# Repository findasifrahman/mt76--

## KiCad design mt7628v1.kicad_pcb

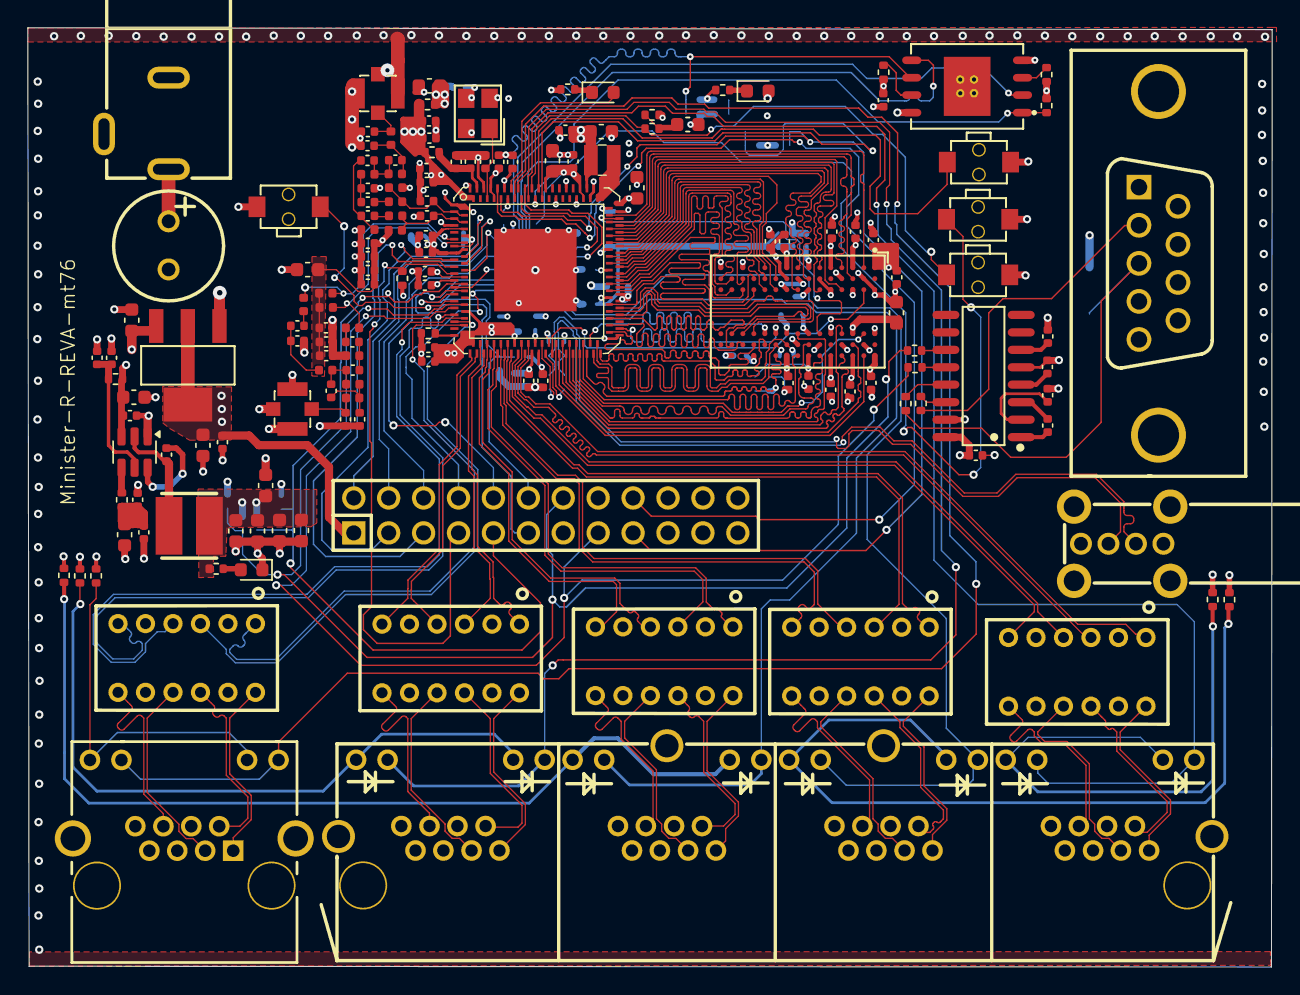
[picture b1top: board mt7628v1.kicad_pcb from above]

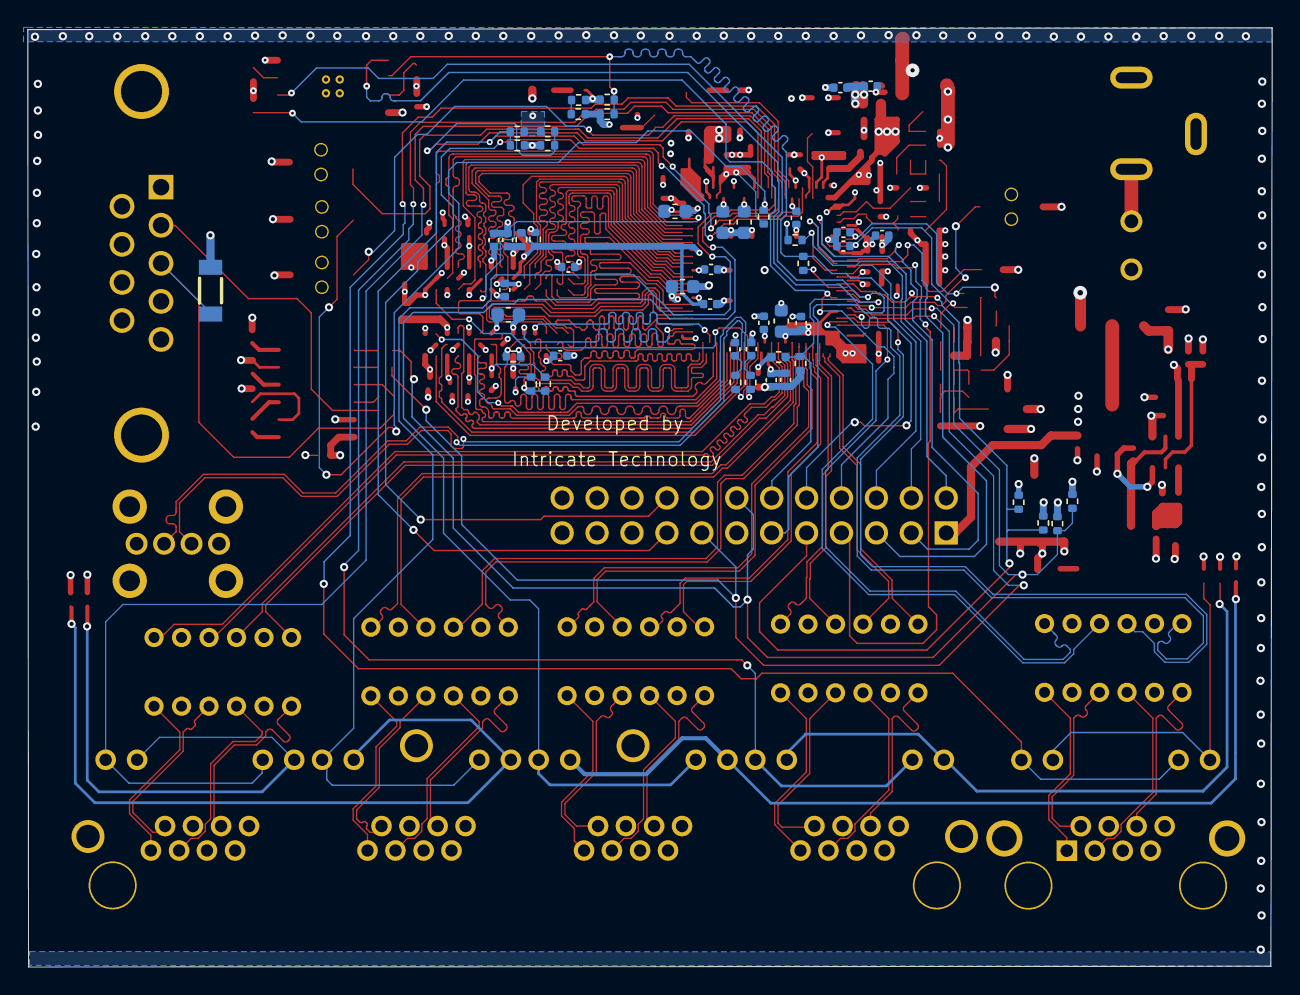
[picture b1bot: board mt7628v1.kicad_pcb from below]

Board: 4 copper layers, 90.5 x 68.3 mm, 201 parts (50 on the bottom side), 176 nets.

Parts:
C1, C2, C4, C5, C6, C7, C14, C15, C16, C18, C21, C25, C26, C29, C34, C35, C36, C37, C38, C39, C40, C70, C71, C76, C85, C95, C96, C97, C98, C99: 100nf/16v; C_0402_1005Metric
C3, C19, C20, C22, C32, C33, C77: 4.7uf/6.3v; C_0603_1608Metric
C8, C10, C11, C17, C30, C43, C45, C47, C48, C51, C61, C66, C81, C82: 1uf/6.3v; C_0402_1005Metric
C9, C27: 2.2uF/6.3V; C_0603_1608Metric
C12, C13: 1.5nf/50V; C_0402_1005Metric
C23, C24: 5pf/50v NC; C_0402_1005Metric
C28, C41, C75: 10uf/6.3v; C_0603_1608Metric
C31: 2.2uf/6.3v; C_0603_1608Metric
C42, C52, C59, C100, C101: 10pf/50v; C_0402_1005Metric
C44, C46, C50, C60, C64, C65, C67, C69, C83: 100pf/50v; C_0402_1005Metric
C49: 10uf/6.3v NC; C_0603_1608Metric
C53, C62, C102, C103: 1.2pf/50v; C_0402_1005Metric
C54, C56, C79, C80: 2pf/50v; C_0402_1005Metric
C55, C104: 9pf/50v; C_0402_1005Metric
C57, C58, C105, C106: 1.8Pf/50v; C_0402_1005Metric
C63: 1.3pf/50v; C_0402_1005Metric
C72, C73: 15pf/50v; C_0402_1005Metric
C74, C89, C90, C91, C92, C93: 22uf/25v; C_0603_1608Metric
C78: 470uf/25v; CAP-TH_BD8.0-P3.50-D0.6-FD
C84: 10uf/25v; C_0603_1608Metric
C86, C87, C94: NC; C_0402_1005Metric
C88: 1uf/25v; C_0402_1005Metric
D1, D2: LED0; LED_0603_1608Metric
D3: LED; D_0603_1608Metric
D4: ZMM5V1; LL-34_L3.5-W1.5-RD
J1: Barrel_Jack_Switch; DC-IN-TH_DC-005C-20A
J2: DE9_Pins; HDR-TH_HL-DP9HB180F
J3: Conn_01x24_MountingPin; HDR-TH_24P-P2.54-V-M-R2-C12-S2.54
J4: RJ45_LED_Shielded_x2; RJ45-TH_DS1128-09-S8B8X
L1: 2.2 uH/VLS252012ET-2R2M; IND-SMD_L2.5-W2.0_VLS2520X
L2, L3, L10, L12: 10nh; L_0402_1005Metric
L4, L9, L15, L16: 2.7nh; L_0402_1005Metric
L5, L7, L8, L13, L14, L18: 2nh; L_0402_1005Metric
L6, L17: 1.2nh; L_0402_1005Metric
L11: 6.8uh; IND-SMD_L4.5-W4.0_GCD43-XX
R1, R2, R3, R4, R5, R6, R7, R25, R26, R27, R28, R29, R30, R31: 4.7k; R_0402_1005Metric
R8: 1K/1%; R_0402_1005Metric
R9: 100nf/1%; R_0402_1005Metric
R10: 100/1%; R_0402_1005Metric
R11, R35: 22; R_0402_1005Metric
R12, R13, R23, R38: 4.7K; R_0402_1005Metric
R14: 24.3K; R_0402_1005Metric
R17: 5.1K/1%; C_0402_1005Metric
R18, R19, R20, R21, R50, R52, R55, R57: 0; R_0402_1005Metric
R22, R24: 10K/1%; R_0402_1005Metric
R32: 10k/1%; R_0402_1005Metric
R33, R40, R41, R42, R43, R44, R47: 1k/1%; R_0402_1005Metric
R34: 20K/1%; R_0402_1005Metric
R36, R37: 330; R_0402_1005Metric
R39: 510/0402; R_0402_1005Metric
R46: 100K/0402; R_0402_1005Metric
R48: 6.2K/0603; C_0603_1608Metric
R49: 2K/0402; C_0402_1005Metric
RF1, RF2: ANT_SHAFT_SEAT; IPEX-SMD_4P-L2.6-W2.6_C9900016457
SW_GPIO1: GPIO; SW-SMD_L3.9-W2.9-LS4.8-EH-A
SW_GPIO3: PORST; SW-SMD_L3.9-W2.9-LS4.8-EH-A
SW_REF_CLK1: REF_CLK; SW-SMD_L3.9-W2.9-LS4.8-EH-A
SW_WDT_RST1: WDT_RST; SW-SMD_L3.9-W2.9-LS4.8-EH-A
U1: W971GG6SB25I; WBGA-84_L12.5-W8.0-P0.80-TL_W9751G6KB
U2: MT7628NN; MT7628_footprint
U3: W25Q256JVEIQ; WSON-8_L8.0-W6.10-P1.27-BL-EP
U4: ams1117-5v; SOT-223_L6.5-W3.5-P2.30-LS7.0-BR
U6: TF-1016DG-LAN4; DIP-12_L12.8-W7.3-P2.00-LS5.0-BL
U7: MP1470; TSOT-23-6
U8: SP3232; SOIC-16_L9.9-W3.9-P1.27-LS6.0-BL
U9: USB_VERTICLE; USB-A-TH_USB-226-BRW
U10: RJ45-TH_B-1-4
U11: TF-1016DG-LAN3; DIP-12_L12.8-W7.3-P2.00-LS5.0-BL
U12: TF-1016DG-LAN2; DIP-12_L12.8-W7.3-P2.00-LS5.0-BL
U13: TF-1016DG-LAN1; DIP-12_L12.8-W7.3-P2.00-LS5.0-BL
U14: TF-1016DG-WAN; DIP-12_L12.8-W7.3-P2.00-LS5.0-BL
Y1: Crystal_40Mhz; CRYSTAL-SMD_4P-L3.2-W2.5-BL

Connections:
3.3VD: C17.1, C18.1, C19.2, C21.1, C22.1, C25.2, C26.2, C27.1, C30.1, C41.1, C42.1, C43.1, C70.1, C71.1, C89.1, C90.1, C91.1, C92.1, C93.1, C94.2, C98.1, J3.24, L11.2, R2.1, R3.1, R5.1, R12.2, R13.2, R20.1, R22.1, R23.2, R24.1, R25.1, R26.1, R28.1, R31.1, R34.2, R36.1, R37.1, R38.1, R39.1, R40.2, R41.2, R42.2, R43.2, R44.2, R48.1, U2.23 (SOC_IO_V33D_1), U2.32 (AVDD33_TX_P0), U2.38 (AVDD33_COM), U2.41 (AVDD33_TX_P1234_1), U2.53 (AVDD33_TX_P1234_2), U2.60 (AVDD33_USB), U2.117 (AVDD33_SMPS), U2.123 (AVDD33_DDRLDO_1), U2.124 (AVDD33_DDRLDO_2), U2.134 (AVDD33_PCIE), U2.146 (SOC_IO_V33D_2), U3.8 (VCC), U8.16 (VCC)
3.3V_RF: C44.1, C45.1, C48.1, C49.1, C50.1, C51.1, C60.1, C61.1, C64.1, C65.1, C66.1, C67.1, C69.1, C81.1, C82.1, C83.1, L2.1, L3.1, L10.1, L12.1, R20.2, R21.1, U2.8 (AVDD33_WF0_TX), U2.14 (AVDD33_WF1_TX), U2.15 (AVDD33_WF1_TRX), U2.149 (AVDD33_WF_RFDIG), U2.150 (AVDD33_XTAL), U2.155 (AVDD33_WF0_TRX)
+5V: C75.1, C76.2, J3.1, U4.2 (VOUT), U4.4 (VOUT)
+12V: C74.1, C78.1, C84.1, C85.1, J1.1, R46.2, U4.3 (VIN), U7.3 (IN)
/ethernet/10: J4.10, J4.12, R44.1
/ethernet/11: R40.1, U10.10, U10.12
/ethernet/12: R41.1, U10.22, U10.24
/ethernet/13: R42.1, U10.34, U10.36
/ethernet/14: R43.1, U10.46, U10.48
/ethernet/RX0N: J4.6, U14.7 (RX-)
/ethernet/RX0P: J4.3, U14.9 (RX+)
/ethernet/RX1N: U6.7 (RX-), U10.6
/ethernet/RX1P: U6.9 (RX+), U10.3
/ethernet/RX2N: U10.18, U11.7 (RX-)
/ethernet/RX2P: U10.15, U11.9 (RX+)
/ethernet/RX3N: U10.30, U12.7 (RX-)
/ethernet/RX3P: U10.27, U12.9 (RX+)
/ethernet/RX4N: U10.42, U13.7 (RX-)
/ethernet/RX4P: U10.39, U13.9 (RX+)
/ethernet/TX0N: J4.2, U14.10 (TX-)
/ethernet/TX0P: J4.1, U14.12 (TX+)
/ethernet/TX1N: U6.10 (TX-), U10.2
/ethernet/TX1P: U6.12 (TX+), U10.1
/ethernet/TX2N: U10.14, U11.10 (TX-)
/ethernet/TX2P: U10.13, U11.12 (TX+)
/ethernet/TX3N: U10.26, U12.10 (TX-)
/ethernet/TX3P: U10.25, U12.12 (TX+)
/ethernet/TX4N: U10.38, U13.10 (TX-)
/ethernet/TX4P: U10.37, U13.12 (TX+)
CLK_N: R10.1, U1.K8 (CK_N), U2.76 (MCK_N)
CLK_P: R10.2, U1.J8 (CK_P), U2.77 (MCK_P)
CPURST_N: R35.1, SW_GPIO3.2, U2.138 (PORST_N)
DDR_BA0: U1.L2 (BA0), U2.100 (MBA0)
DDR_BA1: U1.L3 (BA1), U2.99 (MBA1)
DDR_BA2: U1.L1 (BA2), U2.101 (MBA2)
DDR_CASN: U1.L7 (~CAS), U2.75 (MCAS)
DDR_CSN: U1.L8 (~CS), U2.78 (MCS)
DDR_IO_1V8_MT7628: C1.2, C3.1, C4.2, C5.2, C6.2, C7.2, C9.1, C10.1, C11.1, C12.1, C13.1, C14.2, C15.2, C16.2, C31.1, C32.1, C37.2, C38.2, C39.2, C40.2, R8.2, R32.1, U1.A1 (VDD), U1.A9 (VDDQ), U1.C1 (VDDQ), U1.C3 (VDDQ), U1.C7 (VDDQ), U1.C9 (VDDQ), U1.E1 (VDD), U1.E9 (VDDQ), U1.G1 (VDDQ), U1.G3 (VDDQ), U1.G7 (VDDQ), U1.G9 (VDDQ), U1.J1 (VDDL), U1.J9 (VDD), U1.M9 (VDD), U1.R1 (VDD), U2.79 (DDR_IO_1V8D_1), U2.98 (DDR_IO_1V8D_2), U2.116 (DDR_IO_1V8D_3), U2.125 (DDRLDO)
DDR_MCKE: U1.K2 (CKE), U2.103 (MCKE)
DDR_MDQM0: U1.F3 (LDM), U2.108 (MDQM0)
DDR_MDQM1: U1.B3 (UDM), U2.64 (MDQM1)
DDR_MDQS0: U1.F7 (LDQS_P), U2.113 (MDQS0)
DDR_MDQS1: U1.B7 (UDQS_P), U2.72 (MDQS1)
DDR_MODT: R32.2, R33.2, U1.K9 (ODT), U2.74 (MODT)
DDR_RASN: U1.K7 (~RAS), U2.81 (MRAS)
DDR_VREF: C1.1, C2.2, C8.1, R8.1, R9.2, U1.J2 (VREF), U2.90 (DDR_IO_VREF_1), U2.104 (DDR_IO_VREF_2)
DDR_WEN: U1.K3 (~WE), U2.102 (MW_E)
GND: C2.1, C3.2, C4.1, C5.1, C6.1, C7.1, C8.2, C9.2, C10.2, C11.2, C12.2, C13.2, C14.1, C15.1, C16.1, C17.2, C18.2, C19.1, C20.1, C21.2, C22.2, C23.2, C24.2, C25.1, C26.1, C27.2, C28.2, C29.1, C30.2, C31.2, C32.2, C33.2, C34.1, C35.1, C36.1, C37.1, C38.1, C39.1, C40.1, C41.2, C42.2, C43.2, C44.2, C45.2, C46.2, C47.2, C48.2, C49.2, C50.2, C51.2, C54.2, C56.2, C57.2, C58.2, C60.2, C61.2, C62.1, C63.2, C64.2, C65.2, C66.2, C67.2, C69.2, C70.2, C71.2, C72.1, C73.2, C74.2, C75.2, C76.1, C77.2, C78.2, C79.2, C80.1, C81.2, C82.2, C83.2, C84.2, C85.2, C86.2, C87.2, C89.2, C90.2, C91.2, C92.2, C93.2, C97.1, C98.2, C99.1, C102.1, C105.2, C106.2, D2.2 (K), D3.1 (K), D4.2 (A), J1.2, J1.3, J2.5, J3.13, J3.16, J3.19, J3.23, J4.SH, L4.1, L15.1, R1.1, R4.1, R6.1, R7.1, R9.1, R14.1, R17.1, R27.1, R29.1, R30.1, R33.1, R49.2, RF1.1, RF1.2, RF2.1, RF2.2, SW_GPIO1.1, SW_GPIO3.1, SW_REF_CLK1.1, SW_WDT_RST1.1, U1.A3 (VSS), U1.A7 (VSSQ), U1.B2 (VSSQ), U1.B8 (VSSQ), U1.D2 (VSSQ), U1.D8 (VSSQ), U1.E3 (VSS), U1.E7 (VSSQ), U1.F2 (VSSQ), U1.F8 (VSSQ), U1.H2 (VSSQ), U1.H8 (VSSQ), U1.J3 (VSS), U1.J7 (VSSDL), U1.N1 (VSS), U1.P9 (VSS), U2.1 (AVSS33_RF_1), U2.2 (AVSS33_RF_2), U2.7 (AVSS33_RF_3), U2.10 (AVSS33_RF_4), U2.13 (AVSS33_RF_5), U2.63 (DDR_IO_VSS_1), U2.115 (DDR_IO_VSS_2), U2.120 (AVSS33_SMPS_1), U2.121 (AVSS33_SMPS_2), U2.128 (PCIE_IO_VSS), U2.152 (AVSS33_XTAL), U2.156 (WF0_LNA_EXT), U3.4 (GND), U3.9, U3.gnd, U4.1 (GND), U7.1 (GND), U8.15 (GND), U9.4 (GND), U9.5 (GND), U9.6 (GND), U9.7 (GND), U9.8 (GND), U10.0, Y1.2, Y1.3, Y1.4
GPIO_0: SW_GPIO1.2, U2.29 (GPIO0)
I2C_SCLK: J3.6, R13.1, U2.20 (I2C_SCLK)
I2C_SD: J3.7, R12.1, U2.21 (I2C_SD)
I2S_CLK: J3.5, U2.19 (I2S_CLK)
I2S_DO: R7.2, R31.2
I2S_SDI: J3.2, U2.16 (I2S_SDI)
I2S_SDO: J3.3, U2.17 (I2S_SDO)
I2S_WS: J3.4, U2.18 (I2S_WS)
LINK0: J4.9, J4.11, U2.143 (EPHY_LED0_N_JTDO)
LINK1: U2.142 (EPHY_LED1_N_JTDI), U10.9, U10.11
LINK2: U2.141 (EPHY_LED2_N_JTMS), U10.21, U10.23
LINK3: U2.140 (AVDD33_TX_P1234_2), U10.33, U10.35
LINK4: U2.139 (EPHY_LED4_N_JTRST_N), U10.45, U10.47
MADDR0: U1.M8 (A0), U2.80 (MA0)
MADDR1: U1.M3 (A1), U2.88 (MA1)
MADDR2: U1.M7 (A2), U2.87 (MA2)
MADDR3: U1.N2 (A3), U2.97 (MA3)
MADDR4: U1.N8 (A4), U2.82 (MA4)
MADDR5: U1.N3 (A5), U2.93 (MA5)
MADDR6: U1.N7 (A6), U2.86 (MA6)
MADDR7: U1.P2 (A7), U2.95 (MA7)
MADDR8: U1.P8 (A8), U2.84 (MA8)
MADDR9: U1.P3 (A9), U2.94 (MA9)
MADDR10: U1.M2 (A10), U2.92 (MA10)
MADDR11: U1.P7 (A11), U2.85 (MA11)
MADDR12: U1.R2 (A12), U2.96 (MA12)
MDATA0: U1.G8 (DQ0), U2.71 (MD0)
MDATA1: U1.G2 (DQ1), U2.107 (MD1)
MDATA2: U1.H7 (DQ2), U2.69 (MD2)
MDATA3: U1.H3 (DQ3), U2.105 (MD3)
MDATA4: U1.H1 (DQ4), U2.106 (MD4)
MDATA5: U1.H9 (DQ5), U2.73 (MD5)
MDATA6: U1.F1 (DQ6), U2.109 (MD6)
MDATA7: U1.F9 (DQ7), U2.70 (MD7)
MDATA8: U1.C8 (DQ8), U2.66 (MD8)
MDATA9: U1.C2 (DQ9), U2.112 (MD9)
MDATA10: U1.D7 (DQ10), U2.68 (MD10)
MDATA11: U1.D3 (DQ11), U2.110 (MD11)
MDATA12: U1.D1 (DQ12), U2.111 (MD12)
MDATA13: U1.D9 (DQ13), U2.67 (MD13)
MDATA14: U1.B1 (DQ14), U2.114 (MD14)
MDATA15: U1.B9 (DQ15), U2.65 (MD15)
unnamed: C52.1, L5.2
unnamed: C52.2, C53.1, L4.2
unnamed: C59.1, L8.2
unnamed: C59.2, C62.2, L9.1
unnamed: C77.1, R34.1, R35.2
unnamed: C94.1, R47.1, R48.2, R49.1
unnamed: C100.1, L13.2
unnamed: C100.2, C103.1, L15.2
unnamed: C101.1, L14.2
unnamed: C101.2, C102.2, L16.1
unnamed: C103.2, C104.1, L16.2, L17.1
unnamed: C104.2, C105.1, L17.2, L18.1
unnamed: C106.1, L18.2, RF2.3
unnamed: D1.1 (A), R36.2
unnamed: D2.1 (A), R37.2
unnamed: D3.2 (A), R39.2
unnamed: C56.1, L3.2, L8.1, U2.3 (WF0_RFION_1), U2.4 (WF0_RFION_2)
unnamed: C54.1, L2.2, L5.1, U2.5 (WF0_RFIOP_1), U2.6 (WF0_RFIOP_2)
unnamed: C63.1, U2.151 (XTALIN), Y1.1
unnamed: R11.2, U2.25 (SPI_CLK)
unnamed: R17.2, U2.59 (USB_VRT)
unnamed: R14.2, U2.39 (EPHY_VRT)
unnamed: L1.1, U2.118 (LXBK_1), U2.119 (LXBK_2)
unnamed: R24.2, U3.7 (~HOLD/~RESET/IO_{3})
unnamed: R22.2, U3.3 (~WP/IO_{2})
unnamed: C88.1, U7.6 (BST)
unnamed: C86.1, C87.1, R46.1, U7.5 (EN)
unnamed: R47.2, U7.4 (FB)
unnamed: C88.2, L11.1, U7.2 (SW)
unnamed: C95.2, U8.1 (C1+)
unnamed: C95.1, U8.3 (C1-)
unnamed: C96.2, U8.4 (C2+)
unnamed: C96.1, U8.5 (C2-)
unnamed: R55.1, U8.13 (R1IN)
unnamed: R52.1, U8.12 (R1OUT)
unnamed: R50.1, U8.11 (T1IN)
unnamed: R57.1, U8.14 (T1OUT)
unnamed: C99.2, U8.2 (V+)
unnamed: C97.2, U8.6 (V-)
PERST_N: R3.2, R30.2, U2.135 (PERST_N)
REF_CLK0: SW_REF_CLK1.2, U2.136 (REF_CLK0)
RFOUT_G0: C55.2, C57.1, L6.2, L7.1
RFOUT_G0_L: C53.2, C55.1, L6.1, L9.2
RX0_232: D4.1 (K), J2.3, R55.2
RXIN0: U2.34 (MDI_RN_P0), U14.4 (RD+)
RXIP0: U2.33 (MDI_RP_P0), U14.6 (RD-)
RXN1: U2.40 (MDI_TP_P1), U6.6 (RD-)
RXN2: U2.45 (MDI_RP_P2), U11.6 (RD-)
RXN3: U2.49 (MDI_TP_P3), U12.6 (RD-)
RXN4: U2.54 (MDI_RP_P4), U13.6 (RD-)
RXP1: U2.42 (MDI_TN_P1), U6.4 (RD+)
RXP2: U2.46 (MDI_RN_P2), U11.4 (RD+)
RXP3: U2.50 (MDI_TN_P3), U12.4 (RD+)
RXP4: U2.55 (MDI_RN_P4), U13.4 (RD+)
SOC_1.2VD_MT7628: C28.1, C29.2, C33.1, C34.2, C35.2, C36.2, C72.2, C73.1, L1.2, U2.22 (SOC_CO_V12D_1), U2.58 (SOC_CO_V12D_2), U2.89 (SOC_CO_V12D_3), U2.91 (SOC_CO_V12D_4), U2.122 (VOUT_FB), U2.145 (SOC_CO_V12D_5)
SOC_1.2VD_MT7688: C20.2, U2.131 (AVDD12_PCIE)
SPI_CLK: J3.10, R2.2, R4.2, R11.1, U3.6 (CLK)
SPI_CS0: J3.8, R23.1, U2.28 (SPI_CS0), U3.1 (~CS)
SPI_CS1: J3.9, R5.2, R6.2, U2.24 (SPI_CS1)
SPI_MISO: J3.11, U2.26 (SPI_MISO), U3.2 (DO/IO_{1})
SPI_MOSI: J3.12, R1.2, R25.2, U2.27 (SPI_MOSI), U3.5 (DI/IO_{0})
TX0_232: J2.2, R57.2
TXN1: U2.43 (MDI_RP_P1), U6.3 (TD-)
TXN2: U2.47 (MDI_TP_P2), U11.3 (TD-)
TXN3: U2.51 (MDI_RP_P3), U12.3 (TD-)
TXN4: U2.56 (MDI_TP_P4), U13.3 (TD-)
TXON0: U2.36 (MDI_TN_P0), U14.1 (TD+)
TXOP0: U2.35 (MDI_TP_P0), U14.3 (TD-)
TXP1: U2.44 (MDI_RN_P1), U6.1 (TD+)
TXP2: U2.48 (MDI_TN_P2), U11.1 (TD+)
TXP3: U2.52 (MDI_RN_P3), U12.1 (TD+)
TXP4: U2.57 (MDI_TN_P4), U13.1 (TD+)
UART_RXD0: J3.15, R52.2, U2.31 (UART_RXD0)
UART_RXD1: J3.18, U2.148 (UART_RXD1)
UART_TXD0: J3.14, R28.2, R29.2, R50.2, U2.30 (UART_TXD0)
UART_TXD1: J3.17, R26.2, R27.2, U2.147 (UART_TXD1)
USB_D+: C23.1, R18.1, U9.3 (D+)
USB_D-: C24.1, R19.1, U9.2 (D-)
USB_DP+: R18.2, U2.61 (USB_DP)
USB_DP-: R19.2, U2.62 (USB_DM)
WDT_RST: R38.2, SW_WDT_RST1.2, U2.137 (WDT_RST_N)
WF0_iPA: C58.1, L7.2, RF1.3
WF1_RF1ON: C80.2, L12.2, L14.1, U2.11 (WF1_RFION)
WF1_RF1OP: C79.1, L10.2, L13.1, U2.12 (WF1_RFIOP)
WF_SX_3V3_IN: C46.1, C47.1, R21.2, U2.154 (AVDD33_WF_SX)
WLED_N: D1.2 (K), U2.144 (WLED_N)

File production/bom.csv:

Designator,Footprint,Quantity,Value,LCSC Part #
"C1, C14, C15, C16, C18, C2, C21, C25, C26, C29, C34, C35, C36, C37, C38, C39, C4, C40, C5, C6, C7, C70, C71, C76, C85, C95, C96, C97, C98, C99",0402,30,100nf/16v,C1525
"C10, C11, C17, C30, C43, C45, C47, C48, C51, C61, C66, C8, C81, C82",0402,14,1uf/6.3v,C15684
"C100, C101, C42, C52, C59",0402,5,10pf/50v,C32949
"C102, C103, C53, C62",0402,4,1.2pf/50v,C1551
"C104, C55",0402,2,9pf/50v,C1580
"C105, C106, C57, C58",0402,4,1.8Pf/50v,C1553
"C12, C13",0402,2,1.5nf/50V,C23967
"C19, C20, C22, C3, C32, C33, C77",0603,7,4.7uf/6.3v,C8032
"C23, C24",0402,2,5pf/50v NC,C1573
"C27, C31, C9",0603,3,2.2uF/6.3V,C71000
"C28, C41, C75",0603,3,10uf/6.3v,C1691
"C44, C46, C50, C60, C64, C65, C67, C69, C83",0402,9,100pf/50v,C1546
C49,0603,1,10uf/6.3v NC,C1691
"C54, C56, C79, C80",0402,4,2pf/50v,C1523
C63,0402,1,1.3pf/50v,C88880
"C72, C73",0402,2,15pf/50v,C1548
"C74, C89, C90, C91, C92, C93",0603,6,22uf/25v,C84419
C78,CAP-TH_BD8.0-P3.50-D0.6-FD,1,470uf/25v,C5154
C84,0603,1,10uf/25v,C13585
"C86, C87, C94",0402,3,NC,
C88,0402,1,1uf/25v,C52923
"D1, D2",0603,2,LED0,C9900005774
D3,0603,1,LED,C2286
D4,LL-34_L3.5-W1.5-RD,1,ZMM5V1,C707194
J1,DC-IN-TH_DC-005C-20A,1,Barrel_Jack_Switch,C84007
J2,HDR-TH_HL-DP9HB180F,1,DE9_Pins,C9900001049
J3,HDR-TH_24P-P2.54-V-M-R2-C12-S2.54,1,Conn_01x24_MountingPin,C358700
J4,RJ45-TH_DS1128-09-S8B8X,1,RJ45_LED_Shielded_x2,C86578
L1,IND-SMD_L2.5-W2.0_VLS2520X,1,2.2 uH/VLS252012ET-2R2M,C107346
"L10, L12, L2, L3",0402,4,10nh,C21585
L11,IND-SMD_L4.5-W4.0_GCD43-XX,1,6.8uh,C10131
"L13, L14, L18, L5, L7, L8",0402,6,2nh,C18216
"L15, L16, L4, L9",0402,4,2.7nh,C76770
"L17, L6",0402,2,1.2nh,C77105
"R1, R12, R13, R2, R23, R26, R29, R3, R38, R6, R7",0402,11,4.7k,C25900
R10,0402,1,100/1%,C25076
"R11, R35",0402,2,22,C25092
R14,0402,1,24.3K,C102920
R17,0402,1,5.1K/1%,C25905
"R18, R19, R20, R21, R50, R52, R55, R57",0402,8,0,C17168
"R22, R24, R32",0402,3,10K/1%,C25744
"R25, R27, R28, R30, R31, R4, R5",0402,7,4.7k,NC
"R33, R40, R41, R42, R43, R44, R47, R8",0402,8,1k/1%,C11702
R34,0402,1,20K/1%,C25545
"R36, R37",0402,2,330,C25104
R39,0402,1,510/0402,C25123
R46,0402,1,100K/0402,C25741
R48,0603,1,6.2K/0603,C4260
R49,0402,1,2K/0402,C4109
R9,0402,1,100nf/1%,C11702
"RF1, RF2",IPEX-SMD_4P-L2.6-W2.6_C9900016457,2,ANT_SHAFT_SEAT,C9900016457
SW_GPIO1,SW-SMD_L3.9-W2.9-LS4.8-EH-A,1,GPIO,C9900006416
SW_GPIO3,SW-SMD_L3.9-W2.9-LS4.8-EH-A,1,PORST,C9900006416
SW_REF_CLK1,SW-SMD_L3.9-W2.9-LS4.8-EH-A,1,REF_CLK,C9900006416
SW_WDT_RST1,SW-SMD_L3.9-W2.9-LS4.8-EH-A,1,WDT_RST,C9900006416
U1,WBGA-84_L12.5-W8.0-P0.80-TL_W9751G6KB,1,W971GG6SB25I,C191947
U10,RJ45-TH_B-1-4,1,~,C138390
U11,DIP-12_L12.8-W7.3-P2.00-LS5.0-BL,1,TF-1016DG-LAN3,C408871
U12,DIP-12_L12.8-W7.3-P2.00-LS5.0-BL,1,TF-1016DG-LAN2,C408871
U13,DIP-12_L12.8-W7.3-P2.00-LS5.0-BL,1,TF-1016DG-LAN1,C408871
U14,DIP-12_L12.8-W7.3-P2.00-LS5.0-BL,1,TF-1016DG-WAN,C408871
U2,MT7628_footprint,1,MT7628NN,C2762437
U3,WSON-8_L8.0-W6.10-P1.27-BL-EP,1,W25Q256JVEIQ,C97522
U4,SOT-223_L6.5-W3.5-P2.30-LS7.0-BR,1,ams1117-5v, C6187
U6,DIP-12_L12.8-W7.3-P2.00-LS5.0-BL,1,TF-1016DG-LAN4,C408871
U7,TSOT-23-6,1,MP1470,C558426
U8,SOIC-16_L9.9-W3.9-P1.27-LS6.0-BL,1,SP3232,C9378
U9,USB-A-TH_USB-226-BRW,1,USB_VERTICLE, C720524
Y1,CRYSTAL-SMD_4P-L3.2-W2.5-BL,1,Crystal_40Mhz,C90924

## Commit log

2025-03-12 updated aux
2025-03-12 init_sch
2025-03-15 f_ver
2025-05-23 final_all_router by asif
